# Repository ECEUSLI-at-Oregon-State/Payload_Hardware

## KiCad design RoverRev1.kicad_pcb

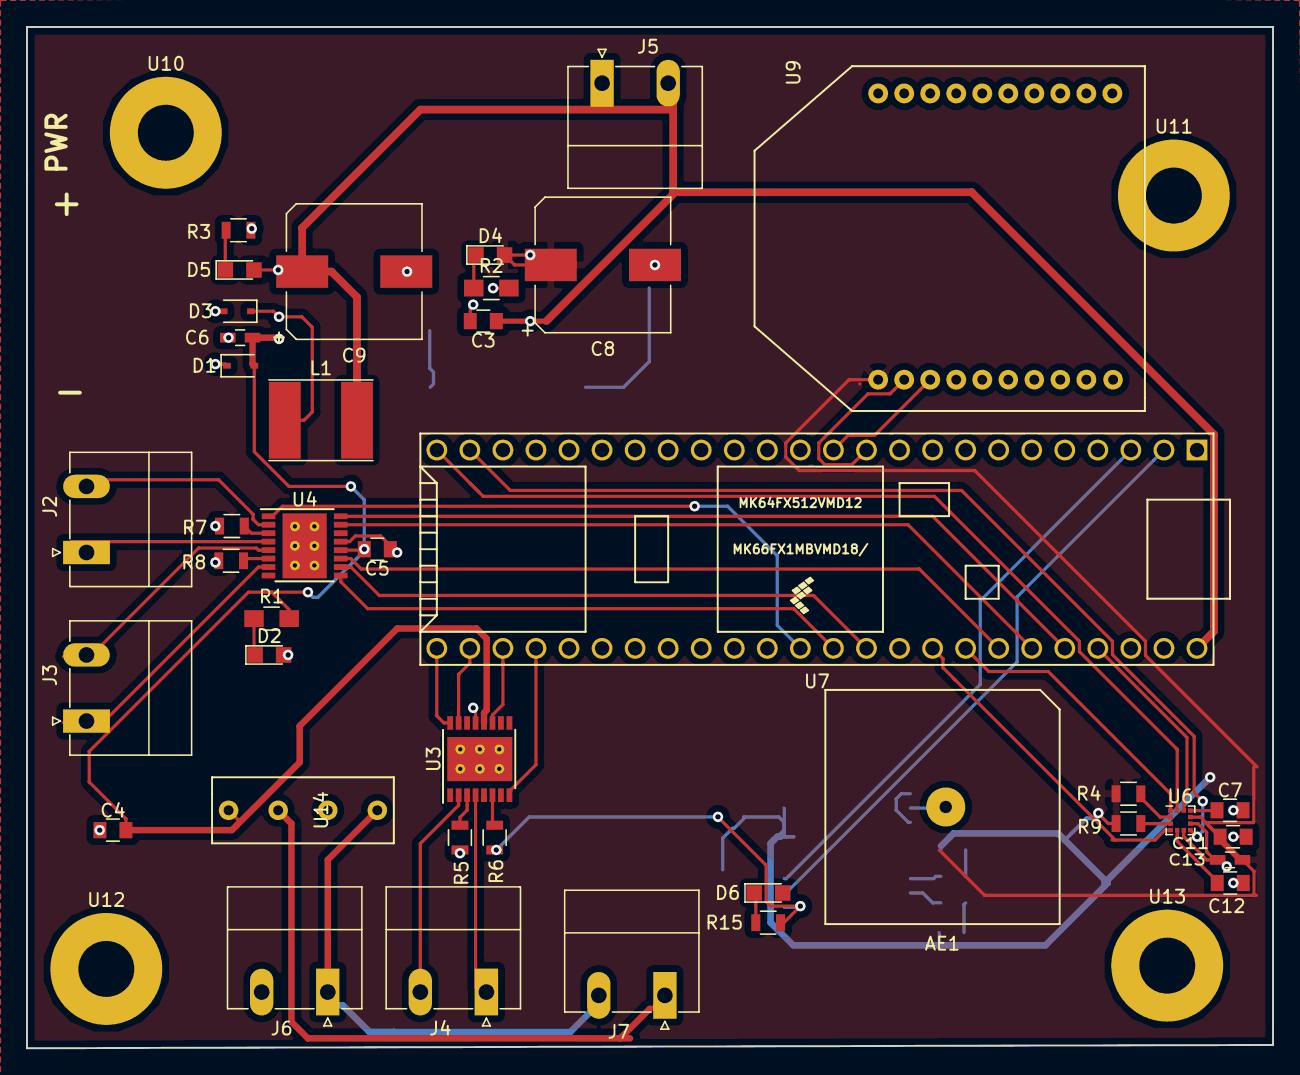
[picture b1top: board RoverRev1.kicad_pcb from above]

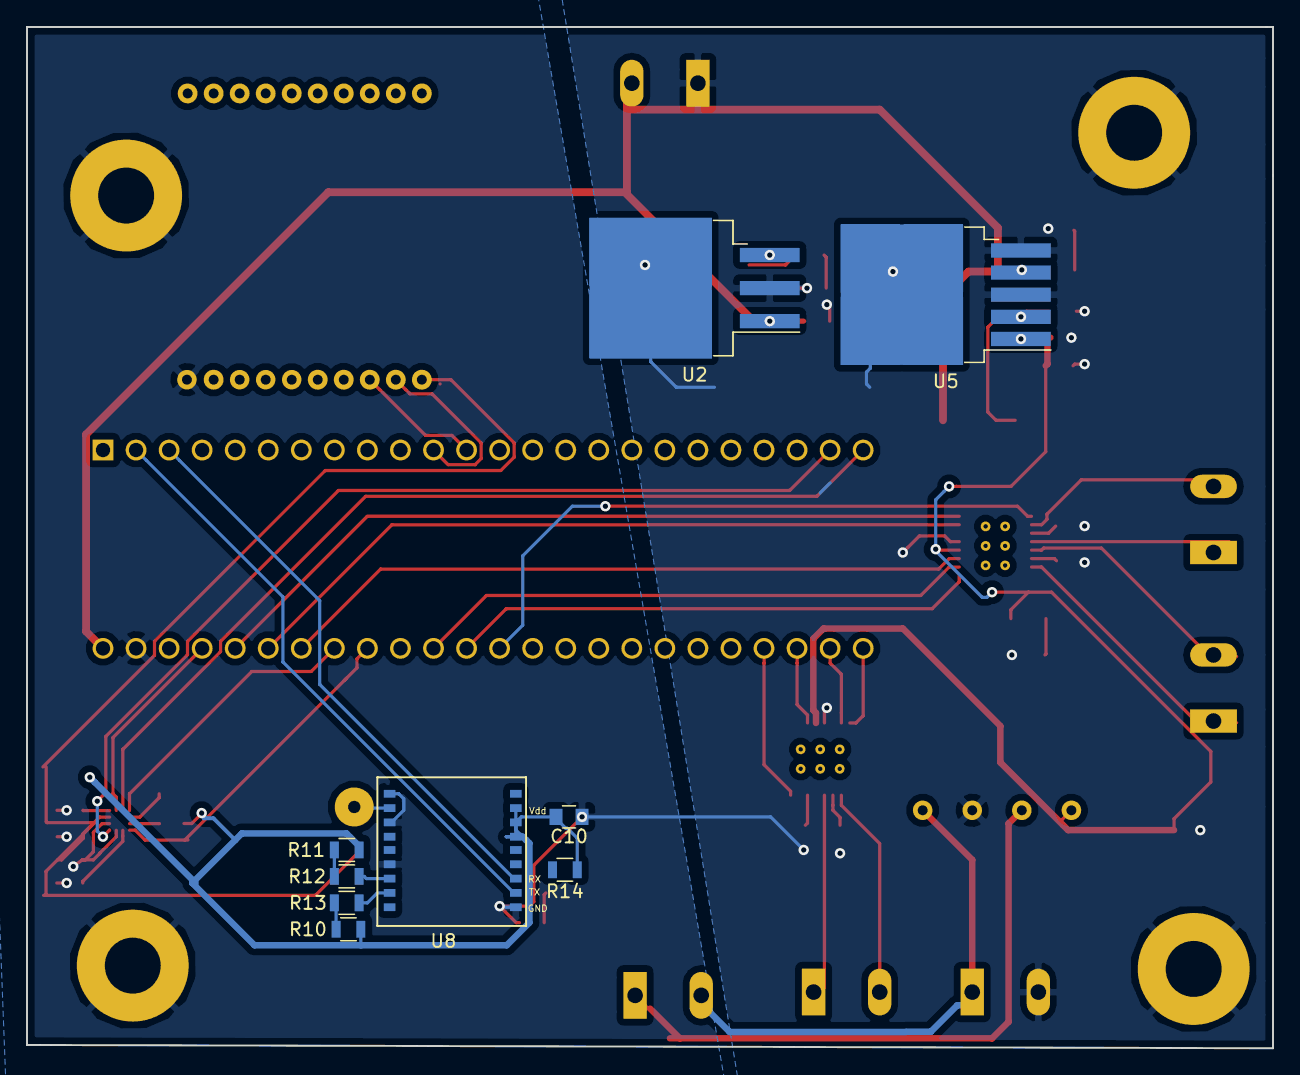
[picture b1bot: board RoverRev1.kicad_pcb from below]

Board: 2 copper layers, 95.8 x 78.5 mm, 53 parts (9 on the bottom side), 49 nets.

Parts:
AE1: Antenna_Shield; GPS-antenna
C3: 0.47u; C_0805
C4, C5: 0.1u; C_0805
C6: 100u; C_0603_HandSoldering
C7, C11: 100n; C_0805
C8: 33u; CP_Elec_10x10
C9: 1000u; CP_Elec_10x10
C10: 10u; C_0805
C12: 220n; C_0805
C13: 0.1u; C_0603_HandSoldering
D1: D; D_SOD-323
D2, D4, D5, D6: LED; LED_0805
D3: D_Schottky; D_SOD-323
J2, J3, J4, J5, J6: Conn_01x02_Male; PhoenixContact_MC-G_02x5.08mm_Angled
J7: Conn_01x02_Female; PhoenixContact_MC-G_02x5.08mm_Angled
L1: 100u; L_Taiyo-Yuden_NR-60xx_HandSoldering
R1: 1K; R_0805_HandSoldering
R2: 500; R_0805_HandSoldering
R3, R15: 500; R_0805
R4, R9: 10K; R_0805
R5, R6, R7, R8: 0.8; R_0805
R10, R11, R14: R_US; R_0805
R12, R13: 22; R_0805
U2: LM3940; TO-263-3_TabPin2
U3, U4: DRV8847; HTSSOP-16-1EP_4.4x5mm_Pitch0.65mm_ThermalVias
U5: LM2576HVS-5; TO-263-5_TabPin3
U6: LSM303C; LGA-12_2x2mm_Pitch0.5mm
U7: Teensy_3.6; Teensy35_36
U8: MAX_M8; MAX-M8Q
U9: XBee-Pro; XBeePro
U10, U11, U12, U13: MountingHoleGen; MountingHole_4.3mm_M4_Pad
U14: Relay3570-1419; Relay 3570

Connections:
+3V3: C8.1, C10.2, C11.2, C13.2, D4.2, R4.2, R9.2, R10.1, R11.1, R14.1, U2.3, U6.9, U8.6, U8.7, U8.8, U9.1
+5V: C3.1, C9.1, D5.2, J5.2, L1.2, U2.1, U5.4, U7.42
+12V: C4.2, C5.2, C6.1, D1.2, R1.2, U3.12, U4.12, U5.1, U14.4
BatteryV: J6.1, J7.2, U14.1
CollFaultN: U3.8, U7.36
CollTorqueControl: U3.11, U7.35
Collection1: J4.2, U3.2
Collection2: J4.1, U3.4
GND: C3.2, C4.1, C5.1, C6.2, C7.2, C8.2, C9.2, C10.1, C11.1, C12.2, C13.1, D1.1, D2.2, D3.2, J5.1, J6.2, R2.2, R3.2, R5.2, R6.2, R7.2, R8.2, R15.2, U2.2, U3.13, U4.13, U5.3, U5.5, U6.6, U6.8, U7.43, U8.1, U8.10, U8.12, U8.15, U9.10, U10.1, U11.1, U12.1, U13.1, U14.2
GPS_RXD: U7.1, U8.3
GPS_SCL: R10.2, R13.2
GPS_SDA: R11.2, R12.2
GPS_TXD: D6.2, U7.0, U8.2
IMU_CS_Acc: R4.1, U6.2
IMU_CS_Mag: R9.1, U6.3
IMU_INT1: U6.7, U7.31
IMU_INT2: U6.12, U7.32
IMU_INT_M: U6.11, U7.23
IMU_SCL: U6.1, U7.19
IMU_SDA: U6.4, U7.18
In1Collection: U3.16, U7.33
In1Motor1: U4.16, U7.22
In2Collection: U3.15, U7.34
In2Motor1: U4.15, U7.21
In3Motor2: U4.9, U7.15
In4Motor2: U4.10, U7.16
Motor1a: J2.2, U4.2
Motor1b: J2.1, U4.4
Motor2a: J3.1, U4.7
Motor2b: J3.2, U4.5
unnamed: AE1.1, U8.11
unnamed: C7.1, U6.10
unnamed: C12.1, U6.5
unnamed: D2.1, R1.1
unnamed: D3.1, L1.1, U5.2
unnamed: D4.1, R2.1
unnamed: D5.1, R3.1
unnamed: D6.1, R15.1
unnamed: J7.1, U14.3
unnamed: R5.1, U3.3
unnamed: R6.1, U3.6
unnamed: R7.1, U4.3
unnamed: R8.1, U4.6
unnamed: R12.1, U8.16
unnamed: R13.1, U8.17
TorqueControl: U4.11, U7.20
TransceiverRx: U7.10, U9.3
TransceiverTx: U7.9, U9.2
nSleepMotor: U4.1, U7.14

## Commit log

2020-05-22 PCB files used in final launch
    This is the version that was used in full scale
